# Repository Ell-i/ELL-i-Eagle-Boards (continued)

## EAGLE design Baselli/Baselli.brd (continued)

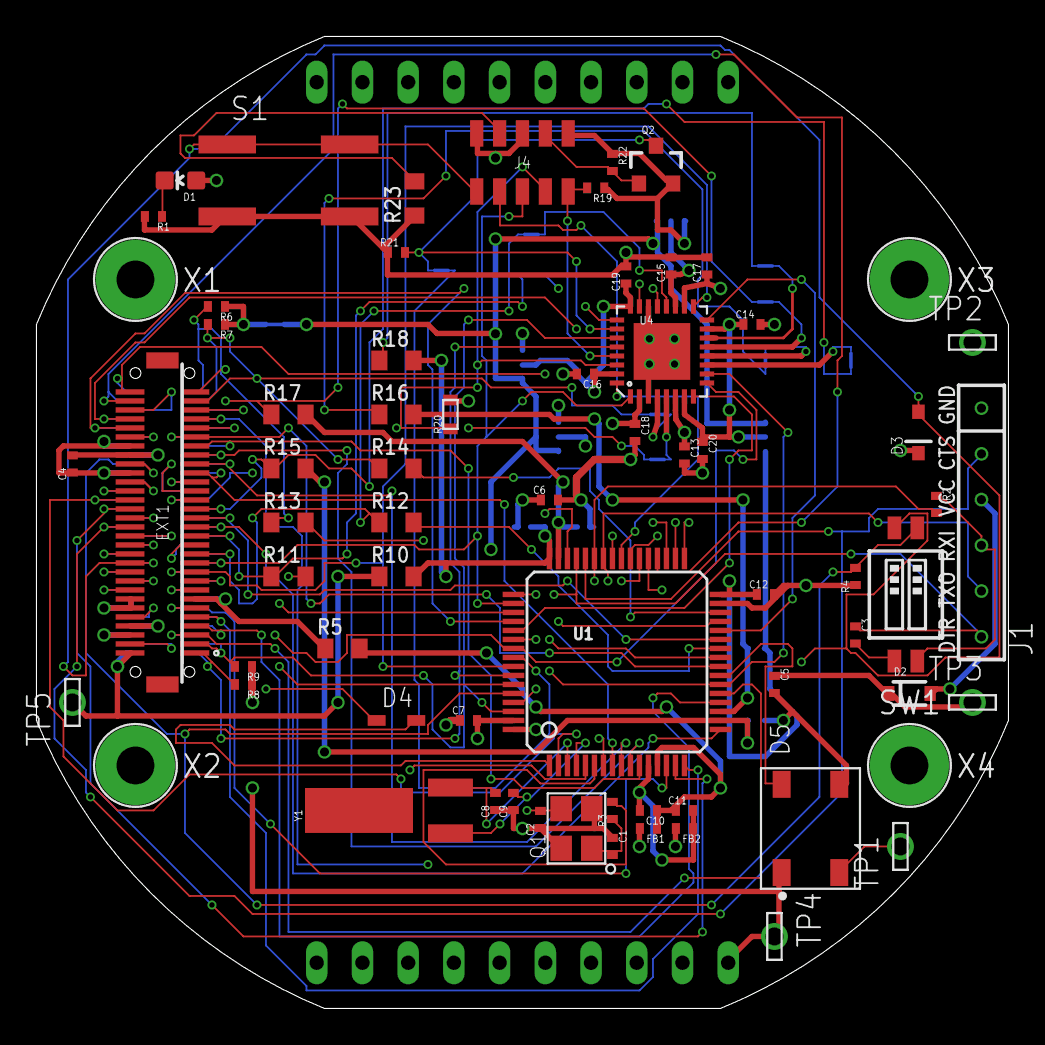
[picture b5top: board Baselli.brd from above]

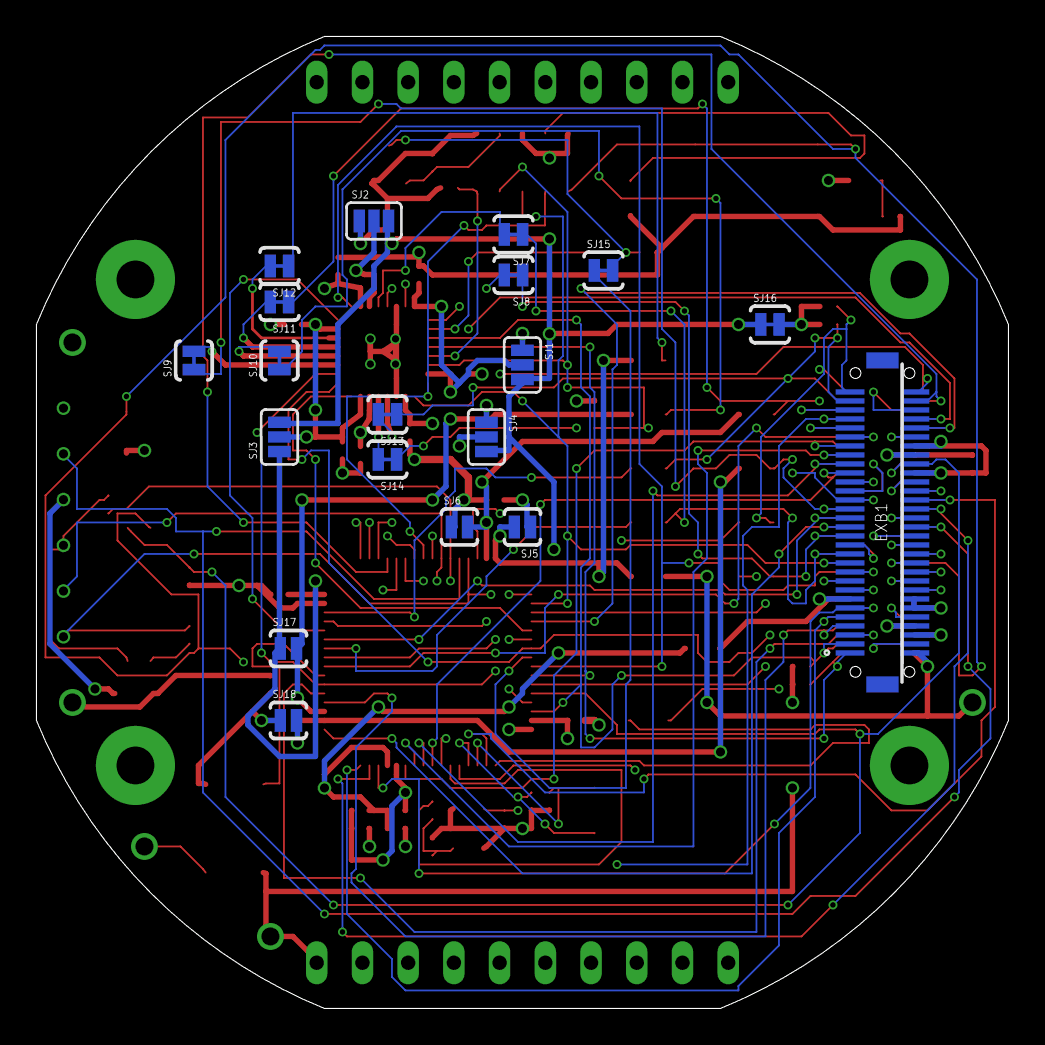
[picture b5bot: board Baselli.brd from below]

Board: 4 copper layers, 54.0 x 54.0 mm, 91 parts (19 on the bottom side), 101 nets.

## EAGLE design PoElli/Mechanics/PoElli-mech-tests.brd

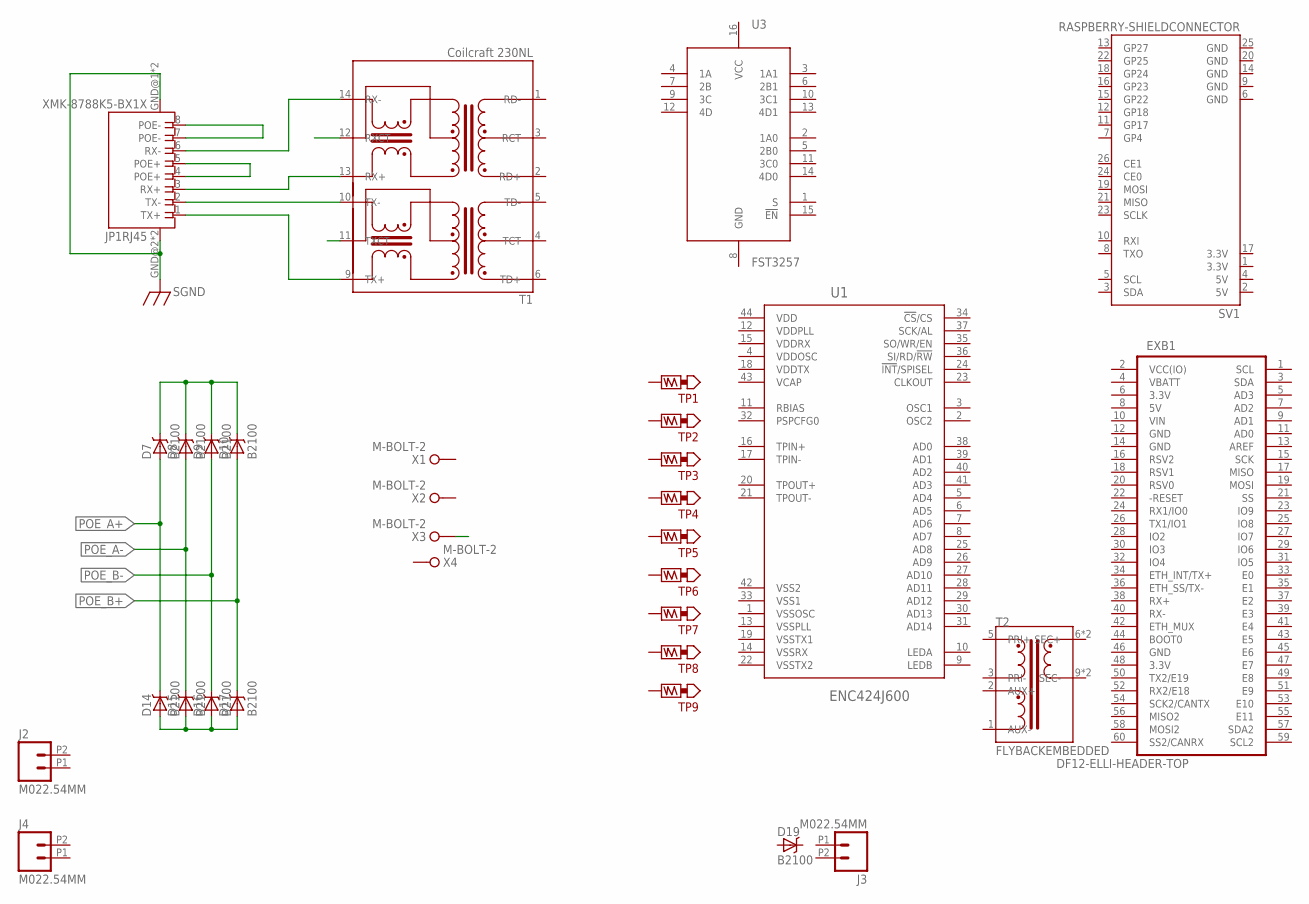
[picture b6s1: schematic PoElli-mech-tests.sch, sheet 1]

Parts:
D7, D8, D9, D10, D14, D15, D16, D17, D19: B2100; DIODE-B2100
EXB1: DF12-ELLI-HEADER-TOP; DF12(4.0)-60DP-0.5V
J2, J3, J4: M022.54MM; 1X02_2.54_SCREWTERM
JP1: XMK-8788K5-BX1X; TE1888250
SV1: RASPBERRY-SHIELDCONNECTOR; RASPBERRYPI-SHIELD-CONNECTOR
T1: Coilcraft 230NL; COILCRAFT-ETH1-230L
T2: FLYBACKEMBEDDED; WE_EP13_SMD_10PIN_EMBEDDED
TP1, TP5, TP6, TP7, TP8, TP9: TEST_POINT-5000; TP_5021
TP2, TP3, TP4: TEST_POINT-5021; TP_5000
U1: ENC424J600; TQFP44-0.8MM
U3: FST3257; SOIC-16-NARROW
X1, X2, X3, X4: M-BOLT-2; M2-1

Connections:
3.3V: EXB1.6 (3.3V), SV1.1 (3.3V), SV1.17 (3.3V)
5V: EXB1.8 (5V), SV1.2 (5V), SV1.4 (5V)
GND: EXB1.12 (GND), EXB1.14 (GND), SV1.6 (GND), SV1.9 (GND), SV1.14 (GND), SV1.20 (GND), SV1.25 (GND), U3.8 (GND)
unnamed: JP1.2 (TX-), T1.10 (TX-)
unnamed: JP1.1 (TX+), T1.9 (TX+)
unnamed: JP1.3 (RX+), T1.13 (RX+)
unnamed: JP1.6 (RX-), T1.14 (RX-)
unnamed: D7.C, D8.C, D9.C, D10.C
unnamed: D14.A, D15.A, D16.A, D17.A
unnamed: JP1.7 (POE-), JP1.8 (POE-)
POE_A+: D7.A, D14.C; also elsewhere on the board
POE_A-: D8.A, D15.C, T1.12 (RXCT); also elsewhere on the board
POE_B+: D10.A, D17.C, JP1.4 (POE+), JP1.5 (POE+); also elsewhere on the board
POE_B-: D9.A, D16.C; also elsewhere on the board
RTN: JP1.GND@1 (GND), JP1.GND@2 (GND), JP1.GND@3 (GND), JP1.GND@4 (GND); also elsewhere on the board
VBATT: EXB1.4 (VBATT)
VCAP: U1.43 (VCAP)
VCC: U3.16 (VCC)
VCC(IO): EXB1.2 (VCC(IO))
VDD: U1.44 (VDD)
VDDOSC: U1.4 (VDDOSC)
VDDPLL: U1.12 (VDDPLL)
VDDRX: U1.15 (VDDRX)
VDDTX: U1.18 (VDDTX)
VIN: EXB1.10 (VIN)
VSS1: U1.33 (VSS1)
VSS2: U1.42 (VSS2)
VSSOSC: U1.1 (VSSOSC)
VSSPLL: U1.13 (VSSPLL)
VSSRX: U1.14 (VSSRX)
VSSTX1: U1.19 (VSSTX1)
VSSTX2: U1.22 (VSSTX2)

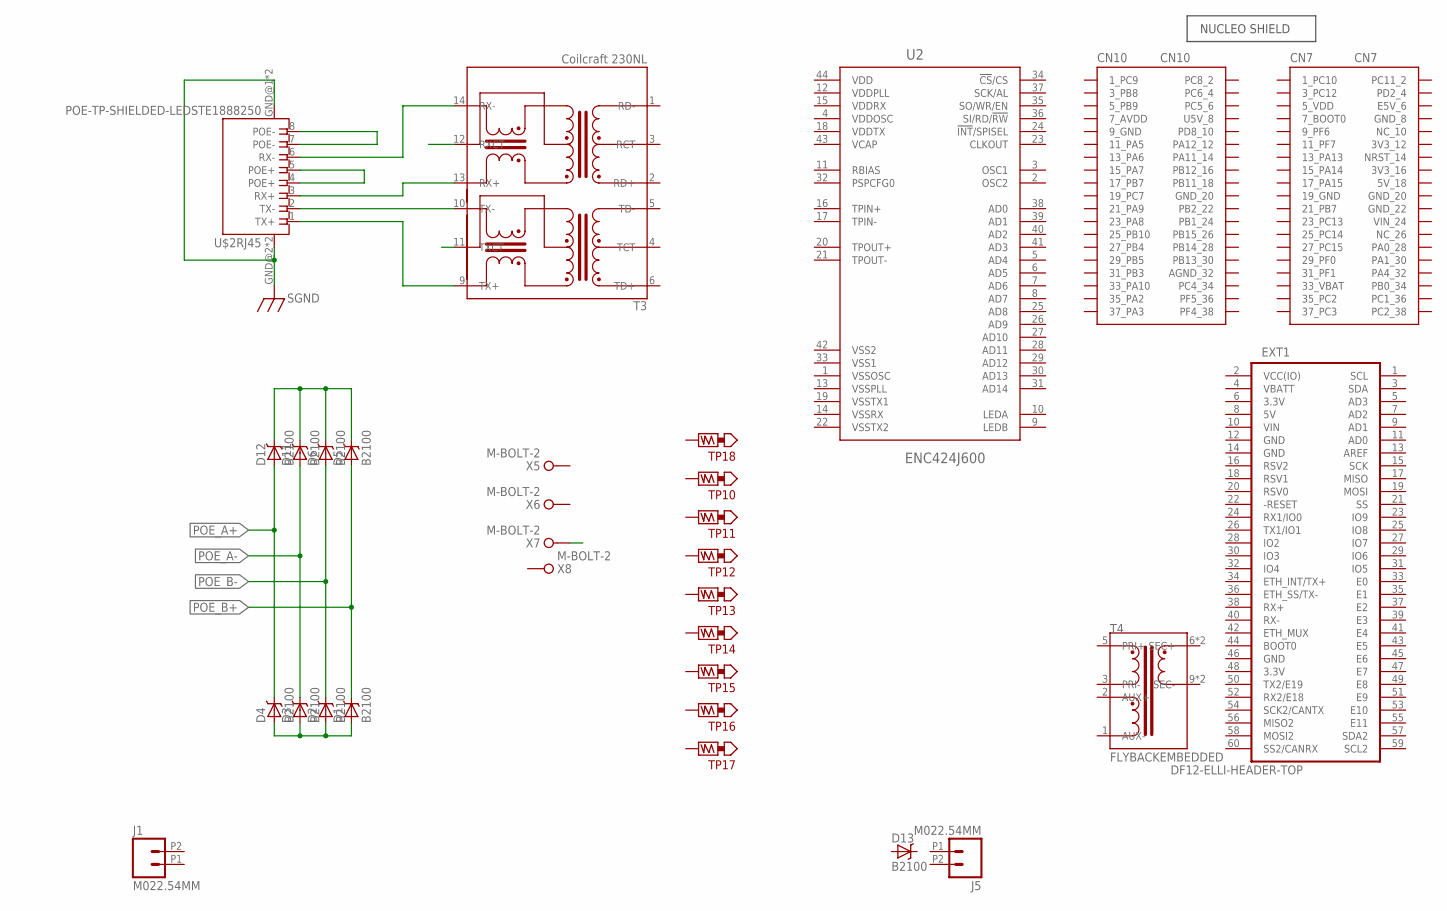
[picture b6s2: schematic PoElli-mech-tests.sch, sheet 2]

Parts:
CN7: NUCLEO-CN7; NUCLEO-HEADER
CN10: NUCLEO-CN10; NUCLEO-HEADER
D1, D2, D3, D4, D5, D6, D11, D12, D13: B2100; DIODE-B2100
EXT1: DF12-ELLI-HEADER-TOP; DF12(4.0)-60DP-0.5V
J1, J5: M022.54MM; 1X02_2.54_SCREWTERM
NUCLEO: NUCLEO-OUTLINE-SHORT; NUCLEO-SHIELD-UNDERSIDE-SHORT-OUTLINE
T3: Coilcraft 230NL; COILCRAFT-ETH1-230L
T4: FLYBACKEMBEDDED; WE_EP13_SMD_10PIN_EMBEDDED
TP10, TP11, TP12: TEST_POINT-5021; TP_5000
TP13, TP14, TP15, TP16, TP17, TP18: TEST_POINT-5000; TP_5021
U2: ENC424J600; TQFP44-0.8MM
U$2: POE-TP-SHIELDED-LEDSTE1888250; TE1888250
X5, X6, X7, X8: M-BOLT-2; M2-1

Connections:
3.3V1: EXT1.6 (3.3V)
5V1: EXT1.8 (5V)
GND1: EXT1.12 (GND), EXT1.14 (GND)
unnamed: T3.10 (TX-), U$2.2 (TX-)
unnamed: T3.9 (TX+), U$2.1 (TX+)
unnamed: T3.13 (RX+), U$2.3 (RX+)
unnamed: T3.14 (RX-), U$2.6 (RX-)
unnamed: D5.C, D6.C, D11.C, D12.C
unnamed: D1.A, D2.A, D3.A, D4.A
unnamed: U$2.7 (POE-), U$2.8 (POE-)
POE_A+: D4.C, D12.A; also elsewhere on the board
POE_A-: D3.C, D11.A, T3.12 (RXCT); also elsewhere on the board
POE_B+: D1.C, D5.A, U$2.4 (POE+), U$2.5 (POE+); also elsewhere on the board
POE_B-: D2.C, D6.A; also elsewhere on the board
RTN: U$2.GND@1 (GND), U$2.GND@2 (GND), U$2.GND@3 (GND), U$2.GND@4 (GND); also elsewhere on the board
VBATT1: EXT1.4 (VBATT)
VCAP1: U2.43 (VCAP)
VCC(IO)1: EXT1.2 (VCC(IO))
VDD1: U2.44 (VDD)
VDDOSC1: U2.4 (VDDOSC)
VDDPLL1: U2.12 (VDDPLL)
VDDRX1: U2.15 (VDDRX)
VDDTX1: U2.18 (VDDTX)
VIN1: EXT1.10 (VIN)
VSS3: U2.42 (VSS2)
VSS4: U2.33 (VSS1)
VSSOSC1: U2.1 (VSSOSC)
VSSPLL1: U2.13 (VSSPLL)
VSSRX1: U2.14 (VSSRX)
VSSTX3: U2.19 (VSSTX1)
VSSTX4: U2.22 (VSSTX2)

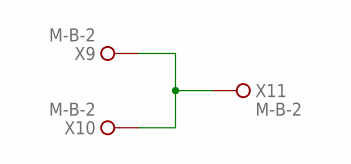
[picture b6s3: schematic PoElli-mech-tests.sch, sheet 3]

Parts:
X9, X10, X11: M-B-2; M2-1

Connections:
PTEST: X9.1, X10.1, X11.1

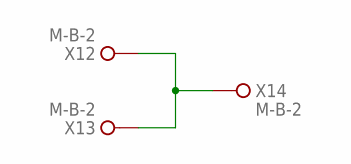
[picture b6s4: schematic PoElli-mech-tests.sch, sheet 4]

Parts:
X12, X13, X14: M-B-2; M2-1

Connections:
PTEST1: X12.1, X13.1, X14.1

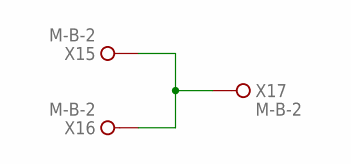
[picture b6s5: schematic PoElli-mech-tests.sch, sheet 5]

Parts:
X15, X16, X17: M-B-2; M2-1

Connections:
PTEST2: X15.1, X16.1, X17.1

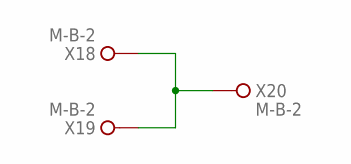
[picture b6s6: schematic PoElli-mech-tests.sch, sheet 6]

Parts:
X18, X19, X20: M-B-2; M2-1

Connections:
PTEST3: X18.1, X19.1, X20.1

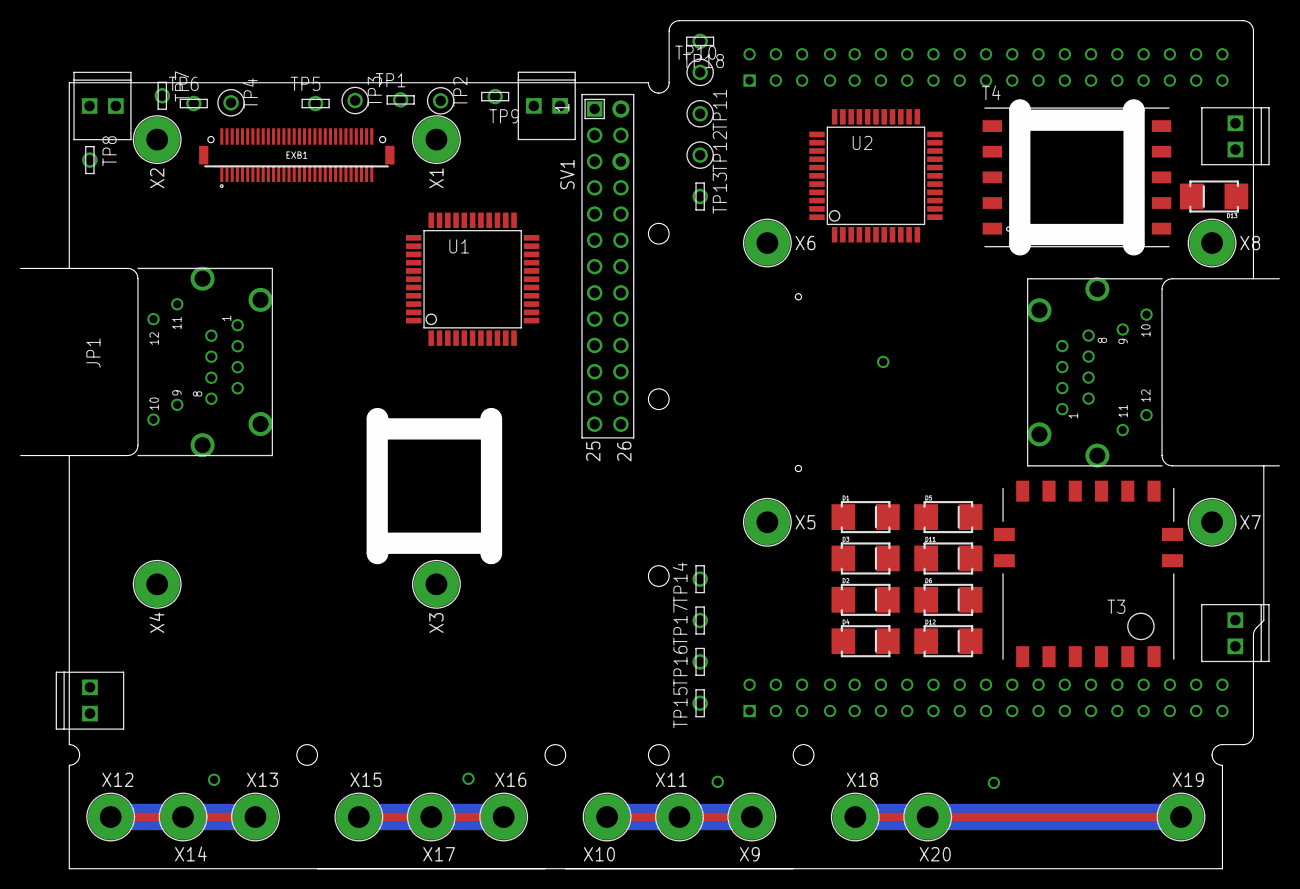
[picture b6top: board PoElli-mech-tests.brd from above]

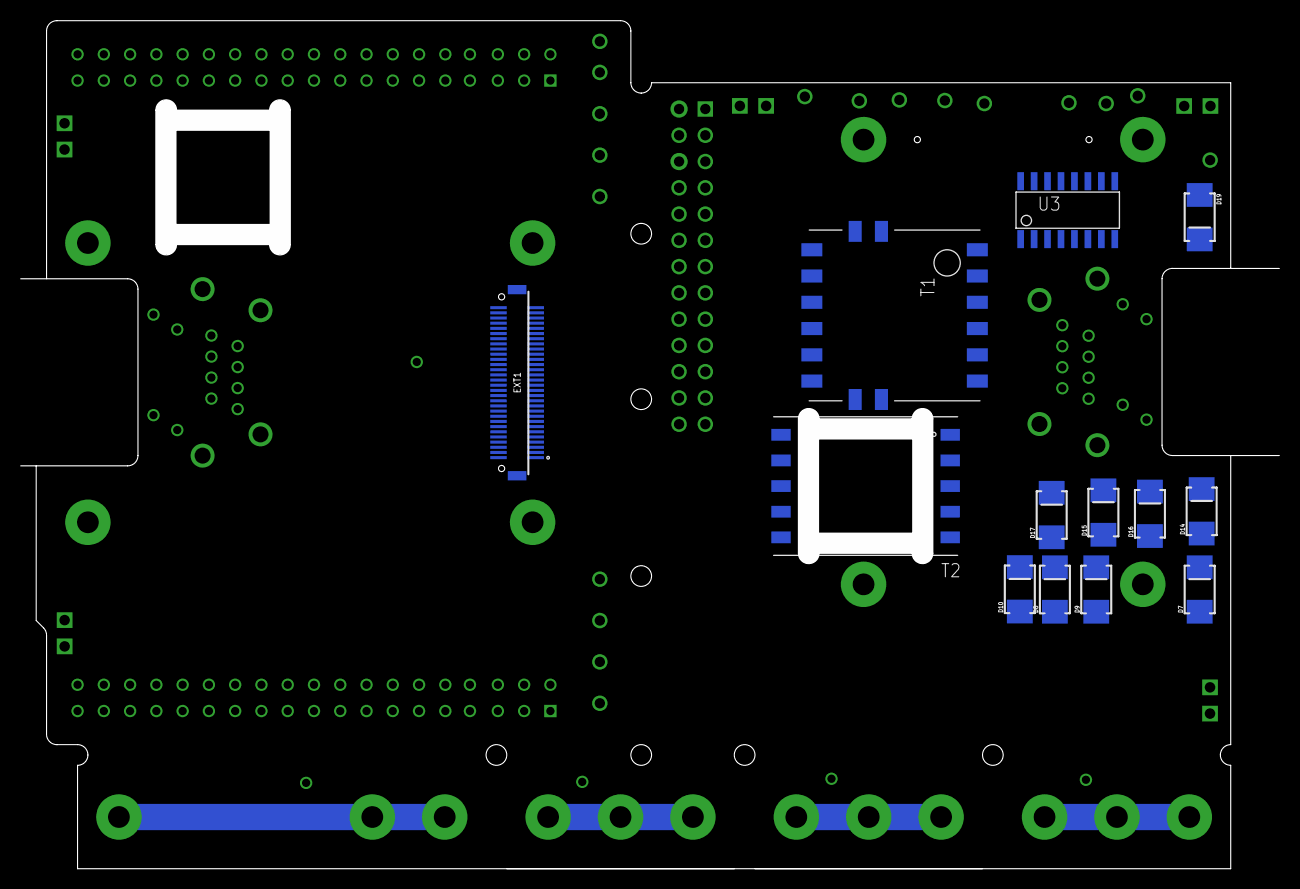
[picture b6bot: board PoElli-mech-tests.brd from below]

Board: 2 copper layers, 119.7 x 80.0 mm, 76 parts (13 on the bottom side), 27 nets.

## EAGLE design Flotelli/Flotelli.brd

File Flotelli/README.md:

Flotelli
========

Ell-i floating-point (STM32F4) series MCU board.

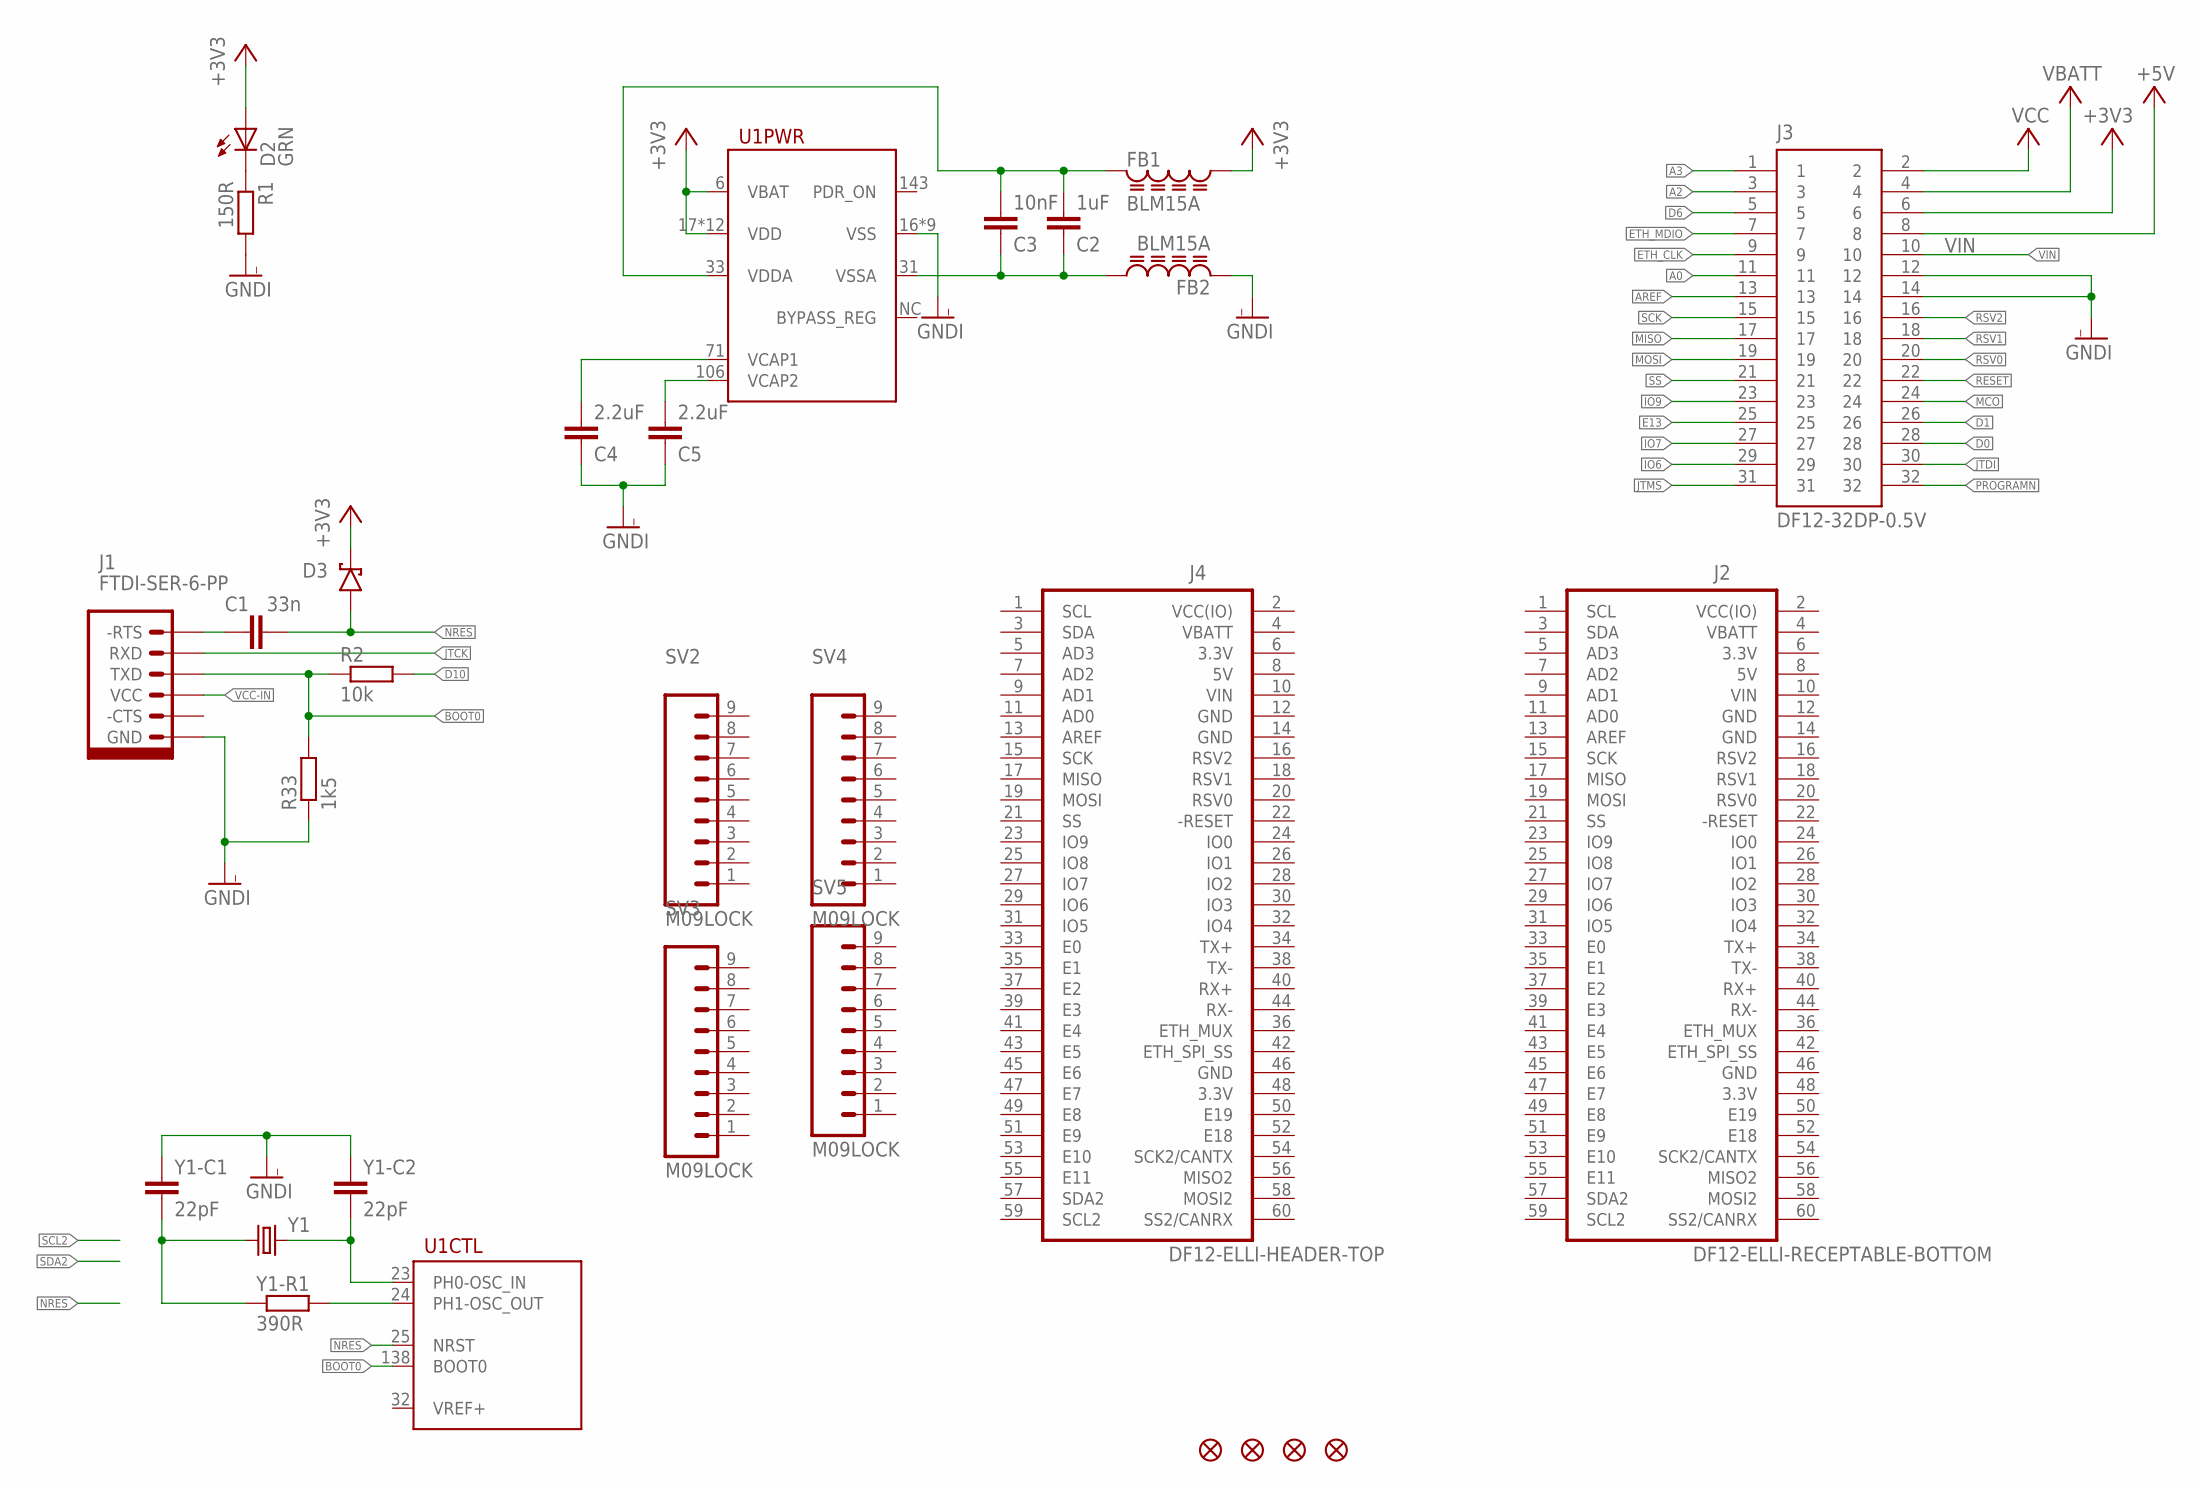
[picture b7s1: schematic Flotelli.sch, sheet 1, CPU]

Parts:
C1: 33n; C0402
C2: 1uF; C0402
C3: 10nF; C0402
C4, C5: 2.2uF; C0402
D2: GRN; LED-0603
D3: BAT60J; SOD323_DIODE
FB1, FB2: BLM15A; 0402
FID1, FID2, FID3, FID4: FIDUCIAL""; FIDUCIAL_1MM
J1: FTDI-SER-6-PP; FTDI-SER-6-SIL
J2: DF12-ELLI-RECEPTABLE-BOTTOM; DF12-60DS-0.5V
J3: DF12-32DP-0.5V; DF12(4.0)-32DP-0.5V
J4: DF12-ELLI-HEADER-TOP; DF12(4.0)-60DP-0.5V
R1: 150R; R0402
R2: 10k; R0402
R33: 1k5; R0402
SV2, SV3, SV4, SV5: M09LOCK; 1X09_LOCK
U1: STM32F429ZIT; LQFP144
Y1: CRYSTALSM49; SM49
Y1-C1, Y1-C2: 22pF; C0402
Y1-R1: 390R; R0402

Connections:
3.3V: J2.6 (3.3V), J4.6 (3.3V)
5V: J2.8 (5V), J4.8 (5V)
+3V3: D2.A, D3.1 (C), FB1.2, J3.6, U1.6 (VBAT), U1.17 (VDD), U1.30 (VDD), U1.39 (VDD), U1.52 (VDD), U1.62 (VDD), U1.72 (VDD), U1.84 (VDD), U1.95 (VDD), U1.108 (VDD), U1.121 (VDD), U1.131 (VDD), U1.144 (VDD); also elsewhere on the board
+5V: J3.8
A0: J3.11; also elsewhere on the board
A2: J3.3; also elsewhere on the board
A3: J3.1; also elsewhere on the board
AREF: J3.13
BOOT0: J1.TXD, R2.1, R33.2, U1.138 (BOOT0)
D0: J3.28; also elsewhere on the board
D1: J3.26; also elsewhere on the board
D6: J3.5; also elsewhere on the board
D10: R2.2; also elsewhere on the board
E13: J3.25; also elsewhere on the board
ETH_CLK: J3.9; also elsewhere on the board
ETH_MDIO: J3.7; also elsewhere on the board
GND: J2.12 (GND), J2.14 (GND), J4.12 (GND), J4.14 (GND)
GNDI: C4.1, C5.1, FB2.1, J1.GND, J3.12, J3.14, R1.2, R33.1, U1.16 (VSS), U1.38 (VSS), U1.51 (VSS), U1.61 (VSS), U1.83 (VSS), U1.94 (VSS), U1.107 (VSS), U1.120 (VSS), U1.130 (VSS), Y1-C1.1, Y1-C2.1; also elsewhere on the board
IO6: J3.29
IO7: J3.27
IO9: J3.23
JTCK: J1.RXD; also elsewhere on the board
JTDI: J3.30; also elsewhere on the board
JTMS: J3.31; also elsewhere on the board
MCO: J3.24; also elsewhere on the board
MISO: J3.17
MOSI: J3.19
N41567: D2.C, R1.1
N98218: C2.1, C3.1, FB2.2, U1.31 (VSSA)
N100630: C2.2, C3.2, FB1.1, U1.33 (VDDA)
N205481: Y1.1, Y1-C1.2, Y1-R1.1
unnamed: C4.2, U1.71 (VCAP1)
unnamed: C5.2, U1.106 (VCAP2)
NDSR2: C1.1, J1.-RTS
NRES: C1.2, D3.2 (A), U1.25 (NRST)
PF0: U1.23 (PH0-OSC_IN), Y1.2, Y1-C2.2
PF1: U1.24 (PH1-OSC_OUT), Y1-R1.2
PROGRAMN: J3.32; also elsewhere on the board
RESET: J3.22
RSV0: J3.20
RSV1: J3.18
RSV2: J3.16
SCK: J3.15
SS: J3.21
VBATT: J2.4 (VBATT), J3.4, J4.4 (VBATT)
VCC: J3.2
VCC(IO): J2.2 (VCC(IO)), J4.2 (VCC(IO))
VCC-IN: J1.VCC
VIN: J2.10 (VIN), J3.10, J4.10 (VIN)

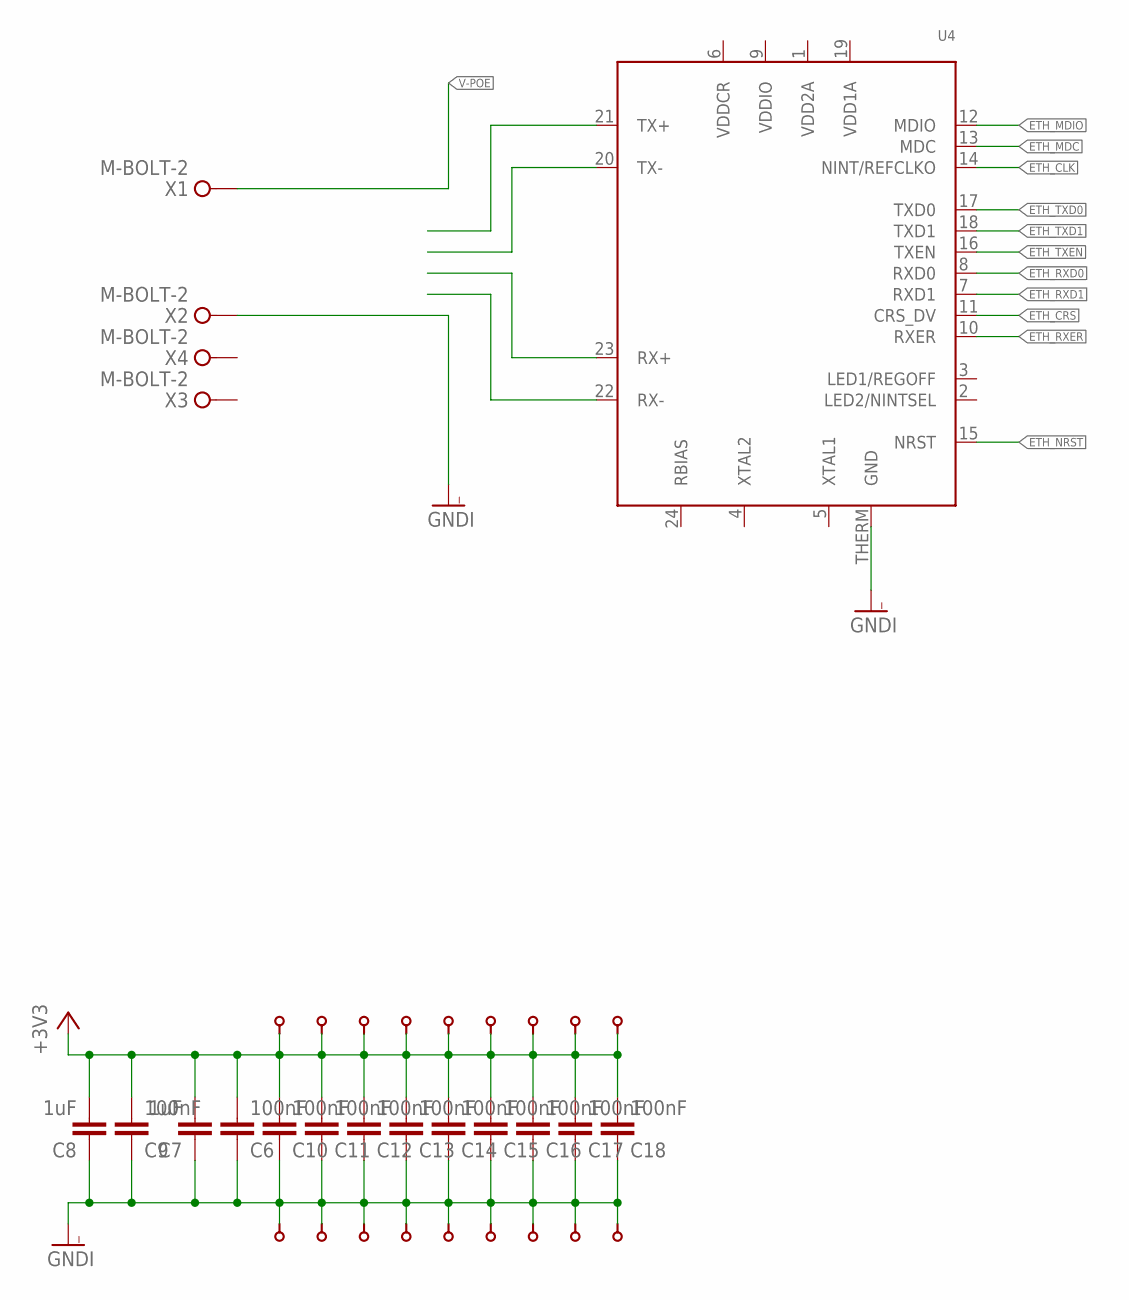
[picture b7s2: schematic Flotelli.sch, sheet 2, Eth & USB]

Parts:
C6, C9, C10, C11, C12, C13, C14, C15, C16, C17, C18: 100nF; C0402
C7, C8: 1uF; C0402
U4: LAN8720-H; QFN-24_4MM-H
VIA1, VIA2, VIA3, VIA4, VIA5, VIA6, VIA7, VIA8, VIA9, VIA10, VIA11, VIA12, VIA13, VIA14, VIA15, VIA16, VIA17, VIA18: VIA-0.3; VIA-0.3MM
X1, X2, X3, X4: M-BOLT-2; M2-1

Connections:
+3V3: C6.2, C7.2, C8.2, C9.2, C10.2, C11.2, C12.2, C13.2, C14.2, C15.2, C16.2, C17.2, C18.2, VIA1.1, VIA2.1, VIA3.1, VIA4.1, VIA5.1, VIA11.1, VIA13.1, VIA15.1, VIA17.1; also elsewhere on the board
ETH_CLK: U4.14 (NINT/REFCLKO); also elsewhere on the board
ETH_CRS: U4.11 (CRS_DV); also elsewhere on the board
ETH_MDC: U4.13 (MDC); also elsewhere on the board
ETH_MDIO: U4.12 (MDIO); also elsewhere on the board
ETH_NRST: U4.15 (NRST)
ETH_RXD0: U4.8 (RXD0); also elsewhere on the board
ETH_RXD1: U4.7 (RXD1); also elsewhere on the board
ETH_RXER: U4.10 (RXER)
ETH_TXD0: U4.17 (TXD0); also elsewhere on the board
ETH_TXD1: U4.18 (TXD1); also elsewhere on the board
ETH_TXEN: U4.16 (TXEN); also elsewhere on the board
GNDI: C6.1, C7.1, C8.1, C9.1, C10.1, C11.1, C12.1, C13.1, C14.1, C15.1, C16.1, C17.1, C18.1, U4.THERM (GND), VIA6.1, VIA7.1, VIA8.1, VIA9.1, VIA10.1, VIA12.1, VIA14.1, VIA16.1, VIA18.1, X2.1; also elsewhere on the board
V-POE: X1.1

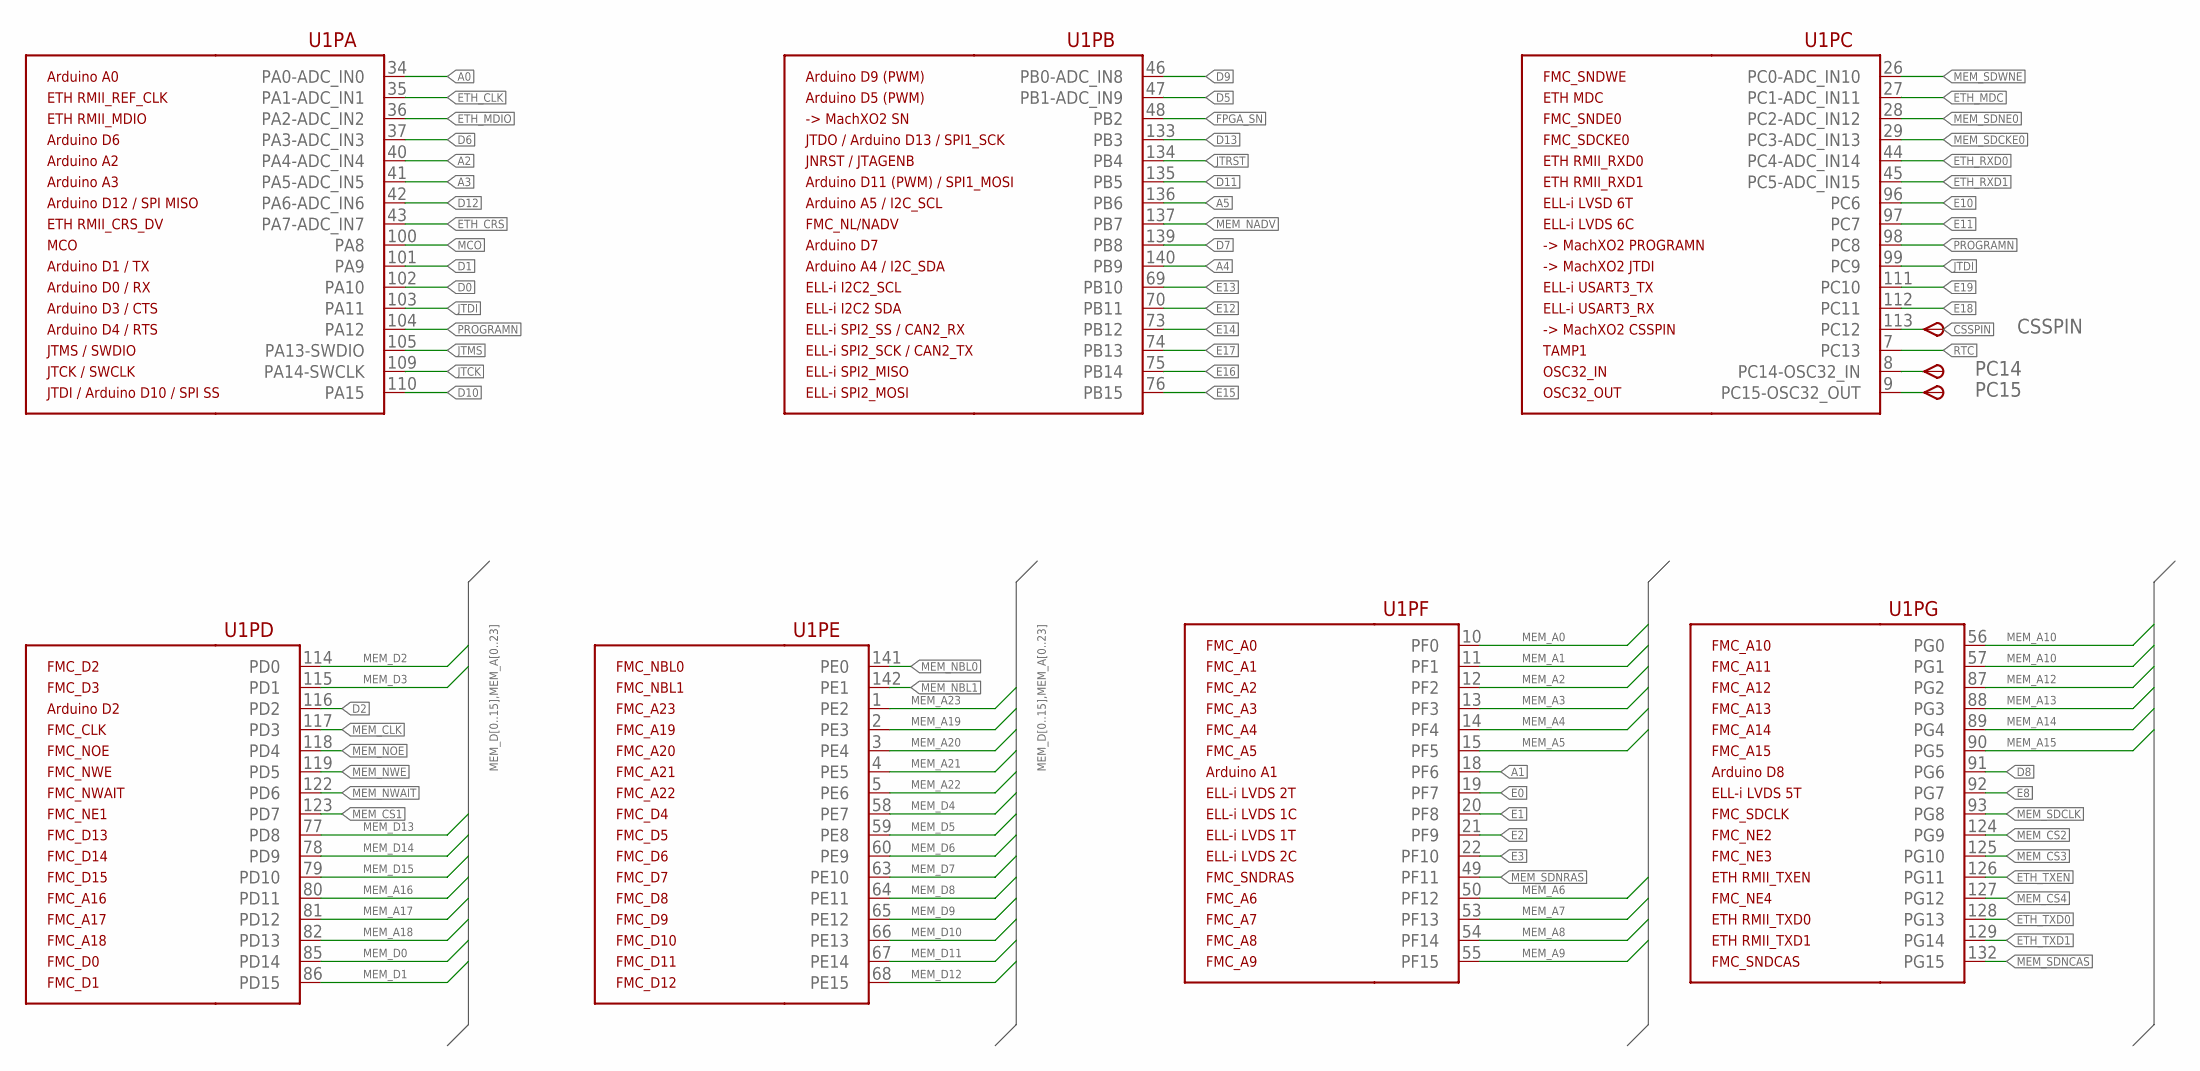
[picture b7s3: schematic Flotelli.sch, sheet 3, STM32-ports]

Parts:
CSSPIN: TPSB1,27; B1,27
PC14, PC15: TPSB1,27; B1,27
U1: STM32F429ZIT; LQFP144

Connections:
A0: U1.34 (PA0-ADC_IN0); also elsewhere on the board
A1: U1.18 (PF6)
A2: U1.40 (PA4-ADC_IN4); also elsewhere on the board
A3: U1.41 (PA5-ADC_IN5); also elsewhere on the board
A4: U1.140 (PB9)
A5: U1.136 (PB6)
CSSPIN: CSSPIN.TP, U1.113 (PC12)
D0: U1.102 (PA10); also elsewhere on the board
D1: U1.101 (PA9); also elsewhere on the board
D2: U1.116 (PD2)
D5: U1.47 (PB1-ADC_IN9)
D6: U1.37 (PA3-ADC_IN3); also elsewhere on the board
D7: U1.139 (PB8)
D8: U1.91 (PG6)
D9: U1.46 (PB0-ADC_IN8)
D10: U1.110 (PA15); also elsewhere on the board
D11: U1.135 (PB5)
D12: U1.42 (PA6-ADC_IN6)
D13: U1.133 (PB3)
E0: U1.19 (PF7)
E1: U1.20 (PF8)
E2: U1.21 (PF9)
E3: U1.22 (PF10)
E8: U1.92 (PG7)
E10: U1.96 (PC6)
E11: U1.97 (PC7)
E12: U1.70 (PB11)
E13: U1.69 (PB10); also elsewhere on the board
E14: U1.73 (PB12)
E15: U1.76 (PB15)
E16: U1.75 (PB14)
E17: U1.74 (PB13)
E18: U1.112 (PC11)
E19: U1.111 (PC10)
ETH_CLK: U1.35 (PA1-ADC_IN1); also elsewhere on the board
ETH_CRS: U1.43 (PA7-ADC_IN7); also elsewhere on the board
ETH_MDC: U1.27 (PC1-ADC_IN11); also elsewhere on the board
ETH_MDIO: U1.36 (PA2-ADC_IN2); also elsewhere on the board
ETH_RXD0: U1.44 (PC4-ADC_IN14); also elsewhere on the board
ETH_RXD1: U1.45 (PC5-ADC_IN15); also elsewhere on the board
ETH_TXD0: U1.128 (PG13); also elsewhere on the board
ETH_TXD1: U1.129 (PG14); also elsewhere on the board
ETH_TXEN: U1.126 (PG11); also elsewhere on the board
FPGA_SN: U1.48 (PB2)
JTCK: U1.109 (PA14-SWCLK); also elsewhere on the board
JTDI: U1.99 (PC9), U1.103 (PA11); also elsewhere on the board
JTMS: U1.105 (PA13-SWDIO); also elsewhere on the board
JTRST: U1.134 (PB4)
MCO: U1.100 (PA8); also elsewhere on the board
MEM_A0: U1.10 (PF0)
MEM_A1: U1.11 (PF1)
MEM_A2: U1.12 (PF2)
MEM_A3: U1.13 (PF3)
MEM_A4: U1.14 (PF4)
MEM_A5: U1.15 (PF5)
MEM_A6: U1.50 (PF12)
MEM_A7: U1.53 (PF13)
MEM_A8: U1.54 (PF14)
MEM_A9: U1.55 (PF15)
MEM_A10: U1.56 (PG0), U1.57 (PG1)
MEM_A12: U1.87 (PG2)
MEM_A13: U1.88 (PG3)
MEM_A14: U1.89 (PG4)
MEM_A15: U1.90 (PG5)
MEM_A16: U1.80 (PD11); also elsewhere on the board
MEM_A17: U1.81 (PD12); also elsewhere on the board
MEM_A18: U1.82 (PD13); also elsewhere on the board
MEM_A19: U1.2 (PE3); also elsewhere on the board
MEM_A20: U1.3 (PE4)
MEM_A21: U1.4 (PE5); also elsewhere on the board
MEM_A22: U1.5 (PE6); also elsewhere on the board
MEM_A23: U1.1 (PE2); also elsewhere on the board
MEM_CLK: U1.117 (PD3)
MEM_CS1: U1.123 (PD7); also elsewhere on the board
MEM_CS2: U1.124 (PG9)
MEM_CS3: U1.125 (PG10)
MEM_CS4: U1.127 (PG12)
MEM_D0: U1.85 (PD14); also elsewhere on the board
MEM_D1: U1.86 (PD15); also elsewhere on the board
MEM_D2: U1.114 (PD0); also elsewhere on the board
MEM_D3: U1.115 (PD1); also elsewhere on the board
MEM_D4: U1.58 (PE7); also elsewhere on the board
MEM_D5: U1.59 (PE8); also elsewhere on the board
MEM_D6: U1.60 (PE9); also elsewhere on the board
MEM_D7: U1.63 (PE10); also elsewhere on the board
MEM_D8: U1.64 (PE11); also elsewhere on the board
MEM_D9: U1.65 (PE12); also elsewhere on the board
MEM_D10: U1.66 (PE13); also elsewhere on the board
MEM_D11: U1.67 (PE14); also elsewhere on the board
MEM_D12: U1.68 (PE15); also elsewhere on the board
MEM_D13: U1.77 (PD8); also elsewhere on the board
MEM_D14: U1.78 (PD9); also elsewhere on the board
MEM_D15: U1.79 (PD10); also elsewhere on the board
MEM_NADV: U1.137 (PB7)
MEM_NBL0: U1.141 (PE0)
MEM_NBL1: U1.142 (PE1)
MEM_NOE: U1.118 (PD4)
MEM_NWAIT: U1.122 (PD6)
MEM_NWE: U1.119 (PD5)
MEM_SDCKE0: U1.29 (PC3-ADC_IN13)
MEM_SDCLK: U1.93 (PG8)
MEM_SDNCAS: U1.132 (PG15)
MEM_SDNE0: U1.28 (PC2-ADC_IN12)
MEM_SDNRAS: U1.49 (PF11)
MEM_SDWNE: U1.26 (PC0-ADC_IN10)
unnamed: PC14.TP, U1.8 (PC14-OSC32_IN)
unnamed: PC15.TP, U1.9 (PC15-OSC32_OUT)
PROGRAMN: U1.98 (PC8), U1.104 (PA12); also elsewhere on the board
RTC: U1.7 (PC13)
